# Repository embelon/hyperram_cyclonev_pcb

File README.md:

# Expansion PCB for Cyclone V SoC Development Kit

Using HSMC connector.

On board:
- 8MB HyperRAM memory: S27KL0641DABHI020
- 16MB HyperFlash : S26KL128SDABHI020
- 4MB QSPI FlashNOR: W25Q32JVSSIQ

I/O
- HDMI output
- 2 x PMOD (3V3): PMOD1 (J6), PMOD2 (7)
- 1 x PMOD (3V3 or 5V): PMOD3 (J5)
- 8bit LA header (shared signals with PMOD3/J5)
- 7 debug signals

### Images

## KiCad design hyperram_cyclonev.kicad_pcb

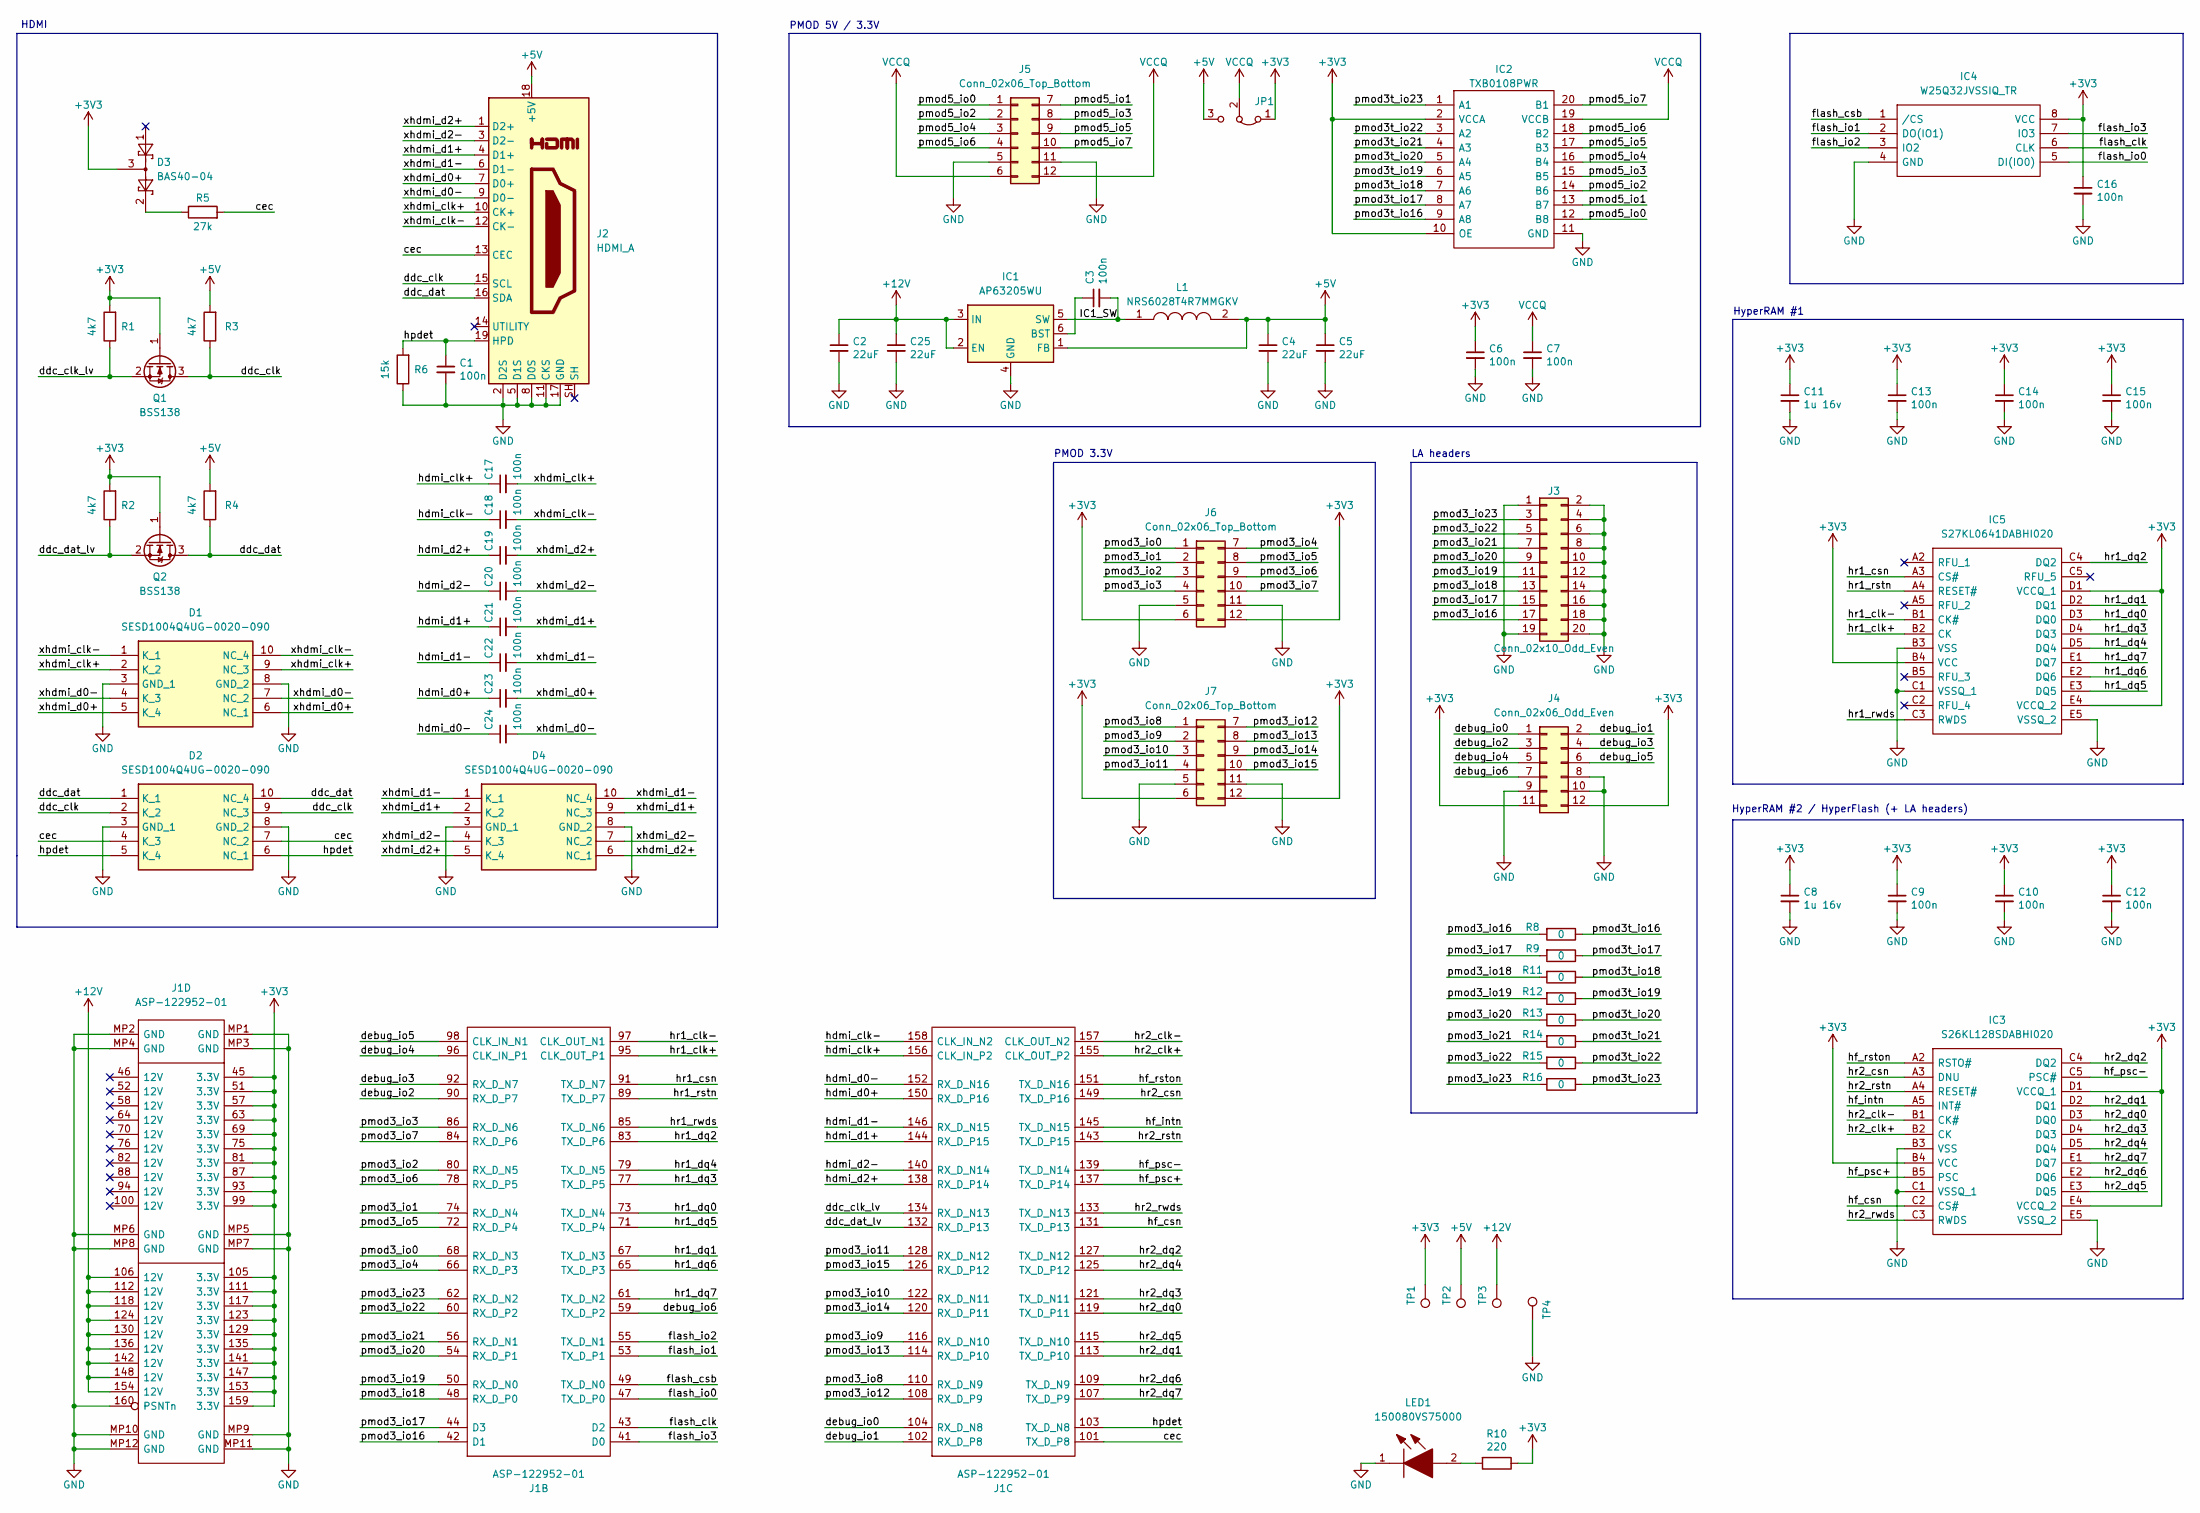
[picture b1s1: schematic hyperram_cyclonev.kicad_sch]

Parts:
C1, C9, C10, C12, C13, C14, C15, C16: 100n; C_0603_1608Metric_Pad1.08x0.95mm_HandSolder; Part CGA3E2X7R1H223K080AA
C2, C4, C5, C25: 22uF; C_0805_2012Metric_Pad1.18x1.45mm_HandSolder; Part CL21A226MAYNNNE
C3, C6, C7: 100n; C_0603_1608Metric_Pad1.08x0.95mm_HandSolder; Part 06033C104KAT2A
C8, C11: 1u 16v; C_0805_2012Metric_Pad1.18x1.45mm_HandSolder; Part CL10A105KO8NNNC
C17, C18, C19, C20, C21, C22, C23, C24: 100n; C_0402_1005Metric_Pad0.74x0.62mm_HandSolder; Part 06033C104KAT2A
D1, D2, D4: SESD1004Q4UG-0020-090; SESD1004Q4UG0020090; Mouser Part Number 650-SESD1004Q4UG0020
D3: BAS40-04; SOT-23
IC1: AP63205WU; TSOT-23-6
IC2: TXB0108PWR; SOP65P640X120-20N; Mouser Part Number 595-TXB0108PWR
IC3: S26KL128SDABHI020; BGA24C100P5X5_600X800X100; Mouser Part Number 727-S26KL128SDABHI02
IC4: W25Q32JVSSIQ_TR; SOIC127P790X216-8N; Mouser Part Number 454-W25Q32JVSSIQTR
IC5: S27KL0641DABHI020; BGA24C100P5X5_600X800X100; Manufacturer_Part_Number S27KL0641DABHI020; Mouser Part Number 727-S27KL0641DABHI02
J1: ASP-122952-01; ASP12295201; Manufacturer_Part_Number ASP-122952-01; Mouser Part Number 200-ASP-122952-01
J2: HDMI_A; 685119134923
J3: Conn_02x10_Odd_Even; PinHeader_2x10_P2.54mm_Vertical
J4: Conn_02x06_Odd_Even; PinHeader_2x06_P2.54mm_Vertical
J5, J6, J7: Conn_02x06_Top_Bottom; 610112249221_PMOD_Bottom
JP1: Jumper_3_Bridged12; PinHeader_1x03_P2.54mm_Vertical
L1: NRS6028T4R7MMGKV; NRS6028T4R7MMGK; Mouser Part Number 963-NRS6028T4R7MMGKV
LED1: 150080VS75000; LEDC2012X80N; Mouser Part Number 710-150080VS75000
Q1, Q2: BSS138; SOT-23
R1, R2, R3, R4: 4k7; R_0603_1608Metric_Pad0.98x0.95mm_HandSolder
R5: 27k; R_0603_1608Metric_Pad0.98x0.95mm_HandSolder
R6: 15k; R_0603_1608Metric_Pad0.98x0.95mm_HandSolder
R8, R9, R11, R12, R13, R14, R15, R16: 0; R_0402_1005Metric_Pad0.72x0.64mm_HandSolder
R10: 220; R_0603_1608Metric_Pad0.98x0.95mm_HandSolder; Part ‎RC0603JR-07100RL‎
TP1: 3V3; TestPoint_Pad_D1.0mm
TP2: 5V; TestPoint_Pad_D1.0mm
TP3: 12V; TestPoint_Pad_D1.0mm
TP4: GND; TestPoint_Pad_D1.0mm

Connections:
+3V3: C6.1, C8.1, C9.1, C10.1, C11.1, C12.1, C13.1, C14.1, C15.1, C16.1, D3.3, IC2.2 (VCCA), IC2.10 (OE), IC3.B4 (VCC), IC3.D1 (VCCQ_1), IC3.E4 (VCCQ_2), IC4.8 (VCC), IC5.B4 (VCC), IC5.D1 (VCCQ_1), IC5.E4 (VCCQ_2), J1.45 (3.3V), J1.51 (3.3V), J1.57 (3.3V), J1.63 (3.3V), J1.69 (3.3V), J1.75 (3.3V), J1.81 (3.3V), J1.87 (3.3V), J1.93 (3.3V), J1.99 (3.3V), J1.105 (3.3V), J1.111 (3.3V), J1.117 (3.3V), J1.123 (3.3V), J1.129 (3.3V), J1.135 (3.3V), J1.141 (3.3V), J1.147 (3.3V), J1.153 (3.3V), J1.159 (3.3V), J4.11, J4.12, J6.6, J6.12, J7.6, J7.12, JP1.1 (A), Q1.1 (G), Q2.1 (G), R1.2, R2.2, R10.1, TP1.1
+5V: C4.1, C5.1, IC1.1 (FB), J2.18 (+5V), JP1.3 (B), L1.2, R3.2, R4.2, TP2.1
+12V: C2.1, C25.1, IC1.2 (EN), IC1.3 (IN), J1.106 (12V), J1.112 (12V), J1.118 (12V), J1.124 (12V), J1.130 (12V), J1.136 (12V), J1.142 (12V), J1.148 (12V), J1.154 (12V), TP3.1
/IC1_SW: C3.2, IC1.5 (SW), L1.1
/cec: D2.4 (K_3), D2.7 (NC_2), J1.101 (TX_D_P8), J2.13 (CEC), R5.2
/ddc_clk: D2.2 (K_2), D2.9 (NC_3), J2.15 (SCL), Q1.3 (D), R3.1
/ddc_clk_lv: J1.134 (RX_D_N13), Q1.2 (S), R1.1
/ddc_dat: D2.1 (K_1), D2.10 (NC_4), J2.16 (SDA), Q2.3 (D), R4.1
/ddc_dat_lv: J1.132 (RX_D_P13), Q2.2 (S), R2.1
/debug_io0: J1.104 (RX_D_N8), J4.1
/debug_io1: J1.102 (RX_D_P8), J4.2
/debug_io2: J1.90 (RX_D_P7), J4.3
/debug_io3: J1.92 (RX_D_N7), J4.4
/debug_io4: J1.96 (CLK_IN_P1), J4.5
/debug_io5: J1.98 (CLK_IN_N1), J4.6
/debug_io6: J1.59 (TX_D_P2), J4.7
/flash_clk: IC4.6 (CLK), J1.43 (D2)
/flash_csb: IC4.1 (/CS), J1.49 (TX_D_N0)
/flash_io0: IC4.5 (DI(IO0)), J1.47 (TX_D_P0)
/flash_io1: IC4.2 (DO(IO1)), J1.53 (TX_D_P1)
/flash_io2: IC4.3 (IO2), J1.55 (TX_D_N1)
/flash_io3: IC4.7 (IO3), J1.41 (D0)
/hdmi_clk+: C17.1, J1.156 (CLK_IN_P2)
/hdmi_clk-: C18.1, J1.158 (CLK_IN_N2)
/hdmi_d0+: C23.1, J1.150 (RX_D_P16)
/hdmi_d0-: C24.1, J1.152 (RX_D_N16)
/hdmi_d1+: C21.1, J1.144 (RX_D_P15)
/hdmi_d1-: C22.1, J1.146 (RX_D_N15)
/hdmi_d2+: C19.1, J1.138 (RX_D_P14)
/hdmi_d2-: C20.1, J1.140 (RX_D_N14)
/hf_csn: IC3.C2 (CS#), J1.131 (TX_D_P13)
/hf_intn: IC3.A5 (INT#), J1.145 (TX_D_N15)
/hf_psc+: IC3.B5 (PSC), J1.137 (TX_D_P14)
/hf_psc-: IC3.C5 (PSC#), J1.139 (TX_D_N14)
/hf_rston: IC3.A2 (RSTO#), J1.151 (TX_D_N16)
/hpdet: C1.1, D2.5 (K_4), D2.6 (NC_1), J1.103 (TX_D_N8), J2.19 (HPD), R6.2
/hr1_clk+: IC5.B2 (CK), J1.95 (CLK_OUT_P1)
/hr1_clk-: IC5.B1 (CK#), J1.97 (CLK_OUT_N1)
/hr1_csn: IC5.A3 (CS#), J1.91 (TX_D_N7)
/hr1_dq0: IC5.D3 (DQ0), J1.73 (TX_D_N4)
/hr1_dq1: IC5.D2 (DQ1), J1.67 (TX_D_N3)
/hr1_dq2: IC5.C4 (DQ2), J1.83 (TX_D_P6)
/hr1_dq3: IC5.D4 (DQ3), J1.77 (TX_D_P5)
/hr1_dq4: IC5.D5 (DQ4), J1.79 (TX_D_N5)
/hr1_dq5: IC5.E3 (DQ5), J1.71 (TX_D_P4)
/hr1_dq6: IC5.E2 (DQ6), J1.65 (TX_D_P3)
/hr1_dq7: IC5.E1 (DQ7), J1.61 (TX_D_N2)
/hr1_rstn: IC5.A4 (RESET#), J1.89 (TX_D_P7)
/hr1_rwds: IC5.C3 (RWDS), J1.85 (TX_D_N6)
/hr2_clk+: IC3.B2 (CK), J1.155 (CLK_OUT_P2)
/hr2_clk-: IC3.B1 (CK#), J1.157 (CLK_OUT_N2)
/hr2_csn: IC3.A3 (DNU), J1.149 (TX_D_P16)
/hr2_dq0: IC3.D3 (DQ0), J1.119 (TX_D_P11)
/hr2_dq1: IC3.D2 (DQ1), J1.113 (TX_D_P10)
/hr2_dq2: IC3.C4 (DQ2), J1.127 (TX_D_N12)
/hr2_dq3: IC3.D4 (DQ3), J1.121 (TX_D_N11)
/hr2_dq4: IC3.D5 (DQ4), J1.125 (TX_D_P12)
/hr2_dq5: IC3.E3 (DQ5), J1.115 (TX_D_N10)
/hr2_dq6: IC3.E2 (DQ6), J1.109 (TX_D_N9)
/hr2_dq7: IC3.E1 (DQ7), J1.107 (TX_D_P9)
/hr2_rstn: IC3.A4 (RESET#), J1.143 (TX_D_P15)
/hr2_rwds: IC3.C3 (RWDS), J1.133 (TX_D_N13)
/pmod3_io0: J1.68 (RX_D_N3), J6.1
/pmod3_io1: J1.74 (RX_D_N4), J6.2
/pmod3_io2: J1.80 (RX_D_N5), J6.3
/pmod3_io3: J1.86 (RX_D_N6), J6.4
/pmod3_io4: J1.66 (RX_D_P3), J6.7
/pmod3_io5: J1.72 (RX_D_P4), J6.8
/pmod3_io6: J1.78 (RX_D_P5), J6.9
/pmod3_io7: J1.84 (RX_D_P6), J6.10
/pmod3_io8: J1.110 (RX_D_N9), J7.1
/pmod3_io9: J1.116 (RX_D_N10), J7.2
/pmod3_io10: J1.122 (RX_D_N11), J7.3
/pmod3_io11: J1.128 (RX_D_N12), J7.4
/pmod3_io12: J1.108 (RX_D_P9), J7.7
/pmod3_io13: J1.114 (RX_D_P10), J7.8
/pmod3_io14: J1.120 (RX_D_P11), J7.9
/pmod3_io15: J1.126 (RX_D_P12), J7.10
/pmod3_io16: J1.42 (D1), J3.17, R8.2
/pmod3_io17: J1.44 (D3), J3.15, R9.2
/pmod3_io18: J1.48 (RX_D_P0), J3.13, R11.2
/pmod3_io19: J1.50 (RX_D_N0), J3.11, R12.2
/pmod3_io20: J1.54 (RX_D_P1), J3.9, R13.2
/pmod3_io21: J1.56 (RX_D_N1), J3.7, R14.2
/pmod3_io22: J1.60 (RX_D_P2), J3.5, R15.2
/pmod3_io23: J1.62 (RX_D_N2), J3.3, R16.2
/pmod3t_io16: IC2.9 (A8), R8.1
/pmod3t_io17: IC2.8 (A7), R9.1
/pmod3t_io18: IC2.7 (A6), R11.1
/pmod3t_io19: IC2.6 (A5), R12.1
/pmod3t_io20: IC2.5 (A4), R13.1
/pmod3t_io21: IC2.4 (A3), R14.1
/pmod3t_io22: IC2.3 (A2), R15.1
/pmod3t_io23: IC2.1 (A1), R16.1
/pmod5_io0: IC2.12 (B8), J5.1
/pmod5_io1: IC2.13 (B7), J5.7
/pmod5_io2: IC2.14 (B6), J5.2
/pmod5_io3: IC2.15 (B5), J5.8
/pmod5_io4: IC2.16 (B4), J5.3
/pmod5_io5: IC2.17 (B3), J5.9
/pmod5_io6: IC2.18 (B2), J5.4
/pmod5_io7: IC2.20 (B1), J5.10
/xhdmi_clk+: C17.2, D1.2 (K_2), D1.9 (NC_3), J2.10 (CK+)
/xhdmi_clk-: C18.2, D1.1 (K_1), D1.10 (NC_4), J2.12 (CK-)
/xhdmi_d0+: C23.2, D1.5 (K_4), D1.6 (NC_1), J2.7 (D0+)
/xhdmi_d0-: C24.2, D1.4 (K_3), D1.7 (NC_2), J2.9 (D0-)
/xhdmi_d1+: C21.2, D4.2 (K_2), D4.9 (NC_3), J2.4 (D1+)
/xhdmi_d1-: C22.2, D4.1 (K_1), D4.10 (NC_4), J2.6 (D1-)
/xhdmi_d2+: C19.2, D4.5 (K_4), D4.6 (NC_1), J2.1 (D2+)
/xhdmi_d2-: C20.2, D4.4 (K_3), D4.7 (NC_2), J2.3 (D2-)
GND: C1.2, C2.2, C4.2, C5.2, C6.2, C7.2, C8.2, C9.2, C10.2, C11.2, C12.2, C13.2, C14.2, C15.2, C16.2, C25.2, D1.3 (GND_1), D1.8 (GND_2), D2.3 (GND_1), D2.8 (GND_2), D4.3 (GND_1), D4.8 (GND_2), IC1.4 (GND), IC2.11 (GND), IC3.B3 (VSS), IC3.C1 (VSSQ_1), IC3.E5 (VSSQ_2), IC4.4 (GND), IC5.B3 (VSS), IC5.C1 (VSSQ_1), IC5.E5 (VSSQ_2), J1.160 (PSNTn), J1.MP1 (GND), J1.MP2 (GND), J1.MP3 (GND), J1.MP4 (GND), J1.MP5 (GND), J1.MP6 (GND), J1.MP7 (GND), J1.MP8 (GND), J1.MP9 (GND), J1.MP10 (GND), J1.MP11 (GND), J1.MP12 (GND), J2.2 (D2S), J2.5 (D1S), J2.8 (D0S), J2.11 (CKS), J2.17 (GND), J3.1, J3.2, J3.4, J3.6, J3.8, J3.10, J3.12, J3.14, J3.16, J3.18, J3.19, J3.20, J4.8, J4.9, J4.10, J5.5, J5.11, J6.5, J6.11, J7.5, J7.11, LED1.1, R6.1, TP4.1
unnamed: D3.2, R5.1
unnamed: C3.1, IC1.6 (BST)
unnamed: LED1.2, R10.2
VCCQ: C7.1, IC2.19 (VCCB), J5.6, J5.12, JP1.2 (C)

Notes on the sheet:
PMOD 3.3V
LA headers
HDMI
HyperRAM #2 / HyperFlash (+ LA headers)
HyperRAM #1
PMOD 5V / 3.3V

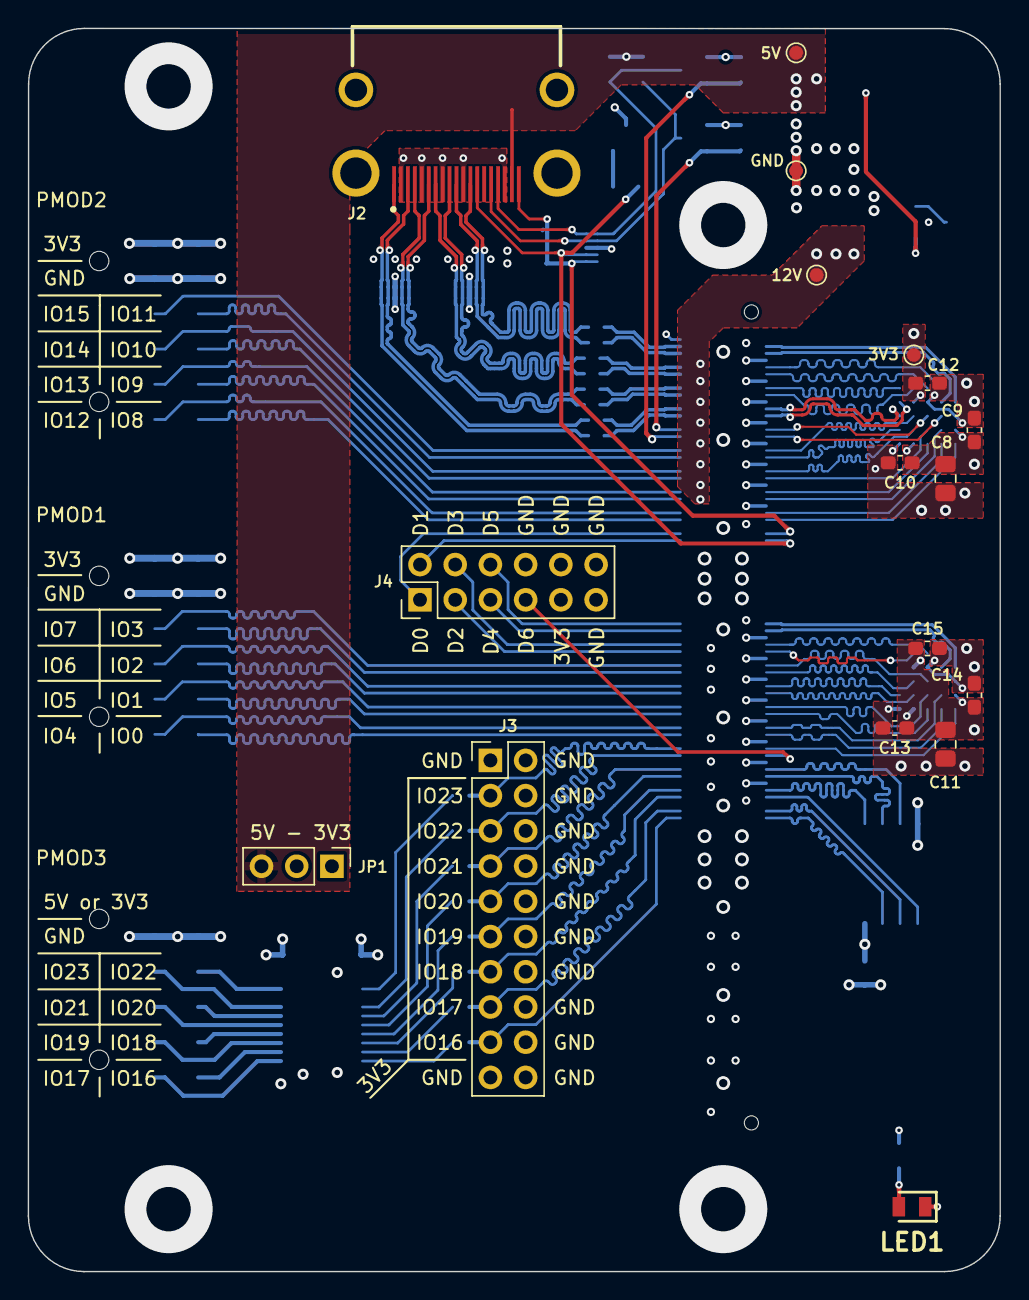
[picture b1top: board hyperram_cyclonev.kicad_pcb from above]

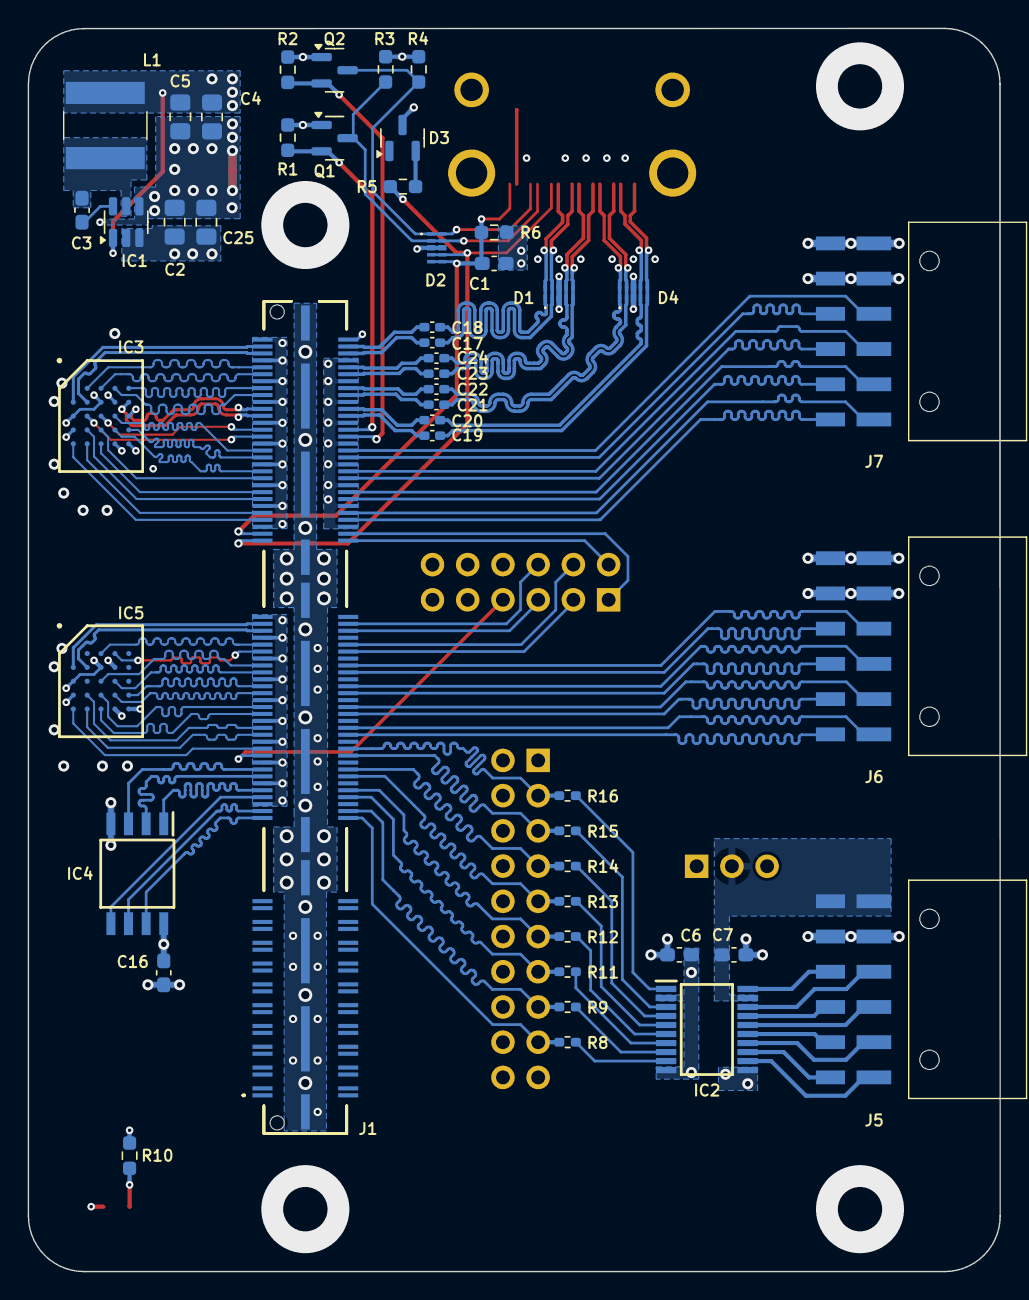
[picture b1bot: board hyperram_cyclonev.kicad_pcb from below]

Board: 4 copper layers, 70.1 x 89.6 mm, 65 parts (48 on the bottom side), 115 nets.

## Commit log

2022-09-15 Added PCB library
2022-10-16 Added DC/DC converter to get 5V for PMOD and HDMI from 12V. Changed two TXB0104 to one TXB0108 for PMOD 5V.
2022-10-24 Updated schematics, made connections between PMODs, HyperBUS devices, Debug Header, QSPI NOR Flash, HDMI and HSMC.
2023-08-11 Migrated to KiCad 7.
2023-08-11 Added 100nF capacitors in series for HDMI signals to get TMDS working with LVDS3 outputs on FPGA.
2023-08-15 Fixed 2 issues with unconnected signals.
2023-08-15 Updated symbols and footprints libraries.
2024-05-12 Fixed Schematics DRC warnings
2024-05-13 Decreased number of ERC complaints. Assigned missing packages.
2024-05-13 Loaded components into PCB.
2024-05-14 Fixed PCB footprint for PMOD
2024-05-14 Updated PCB footprint for HSMC
2024-05-14 Simplified schematic, removing unnecessary elements
2024-05-14 Created edge.cuts. Updated PCB from schematic.
2024-05-15 Fixed issue with PMOD pins assignment
2024-05-16 Adjusted PCB dimensions. Moved components to the back side
2024-05-17 Changed two connectors from SMD to THT
2024-05-17 Rearrange signals assignments to simplify routing.
2024-05-17 Changed footprint in library from SMD to THT
2024-05-17 Added modified pinouts for PMOD, top and bottom version
2024-05-17 Reaarranged signals assignments to simplify routing
2024-05-22 Set constraints for PCBWay: 6/6mil, hole 0.25mm. First try for routing HyperRAM with trace length matching.
2024-05-23 Optimizing signal assigments and component placement to simplify routing.
2024-05-27 Fixed differential pairs designators for HyperRAM clk and psc and HDMI clk and data.
2024-06-11 Changed order of HDMI data signals to avoid crossing
2024-06-11 Decreased board area. Fixed HyperRAM clk diff pair routing. First try for HDMI diff pair routing.
2024-06-12 Added additional resistors on LA / PMOD path
2024-06-12 Routed almost all single ended signals, except HDMI and power
2024-06-13 Added net class for HDMI differential signals
2024-06-13 Routed HDMI differential signals for a first time, still with unmatched lenghts between pairs
2024-06-14 Added width/space definition for differential traces
2024-06-14 Fixed pin numbering for SESD Series TVS Diode Array
2024-06-14 Fixed signals connection to SESD Series TVS Diode Array
2024-06-14 Decreased courtyyard/keepout area for SESD Series TVS Diode Array in DFN 0802 package
2024-06-14 Fixed path to package definition library from absolute to relative
2024-06-14 Updated PCB with latest fixes in schematic related to SESD Series TVS Diode Array
2024-06-18 Added symbol for new component SESD1004, TVS Diode Array, to the library
2024-06-18 Added footprint for new component SESD1004, TVS Diode Array, to the library
2024-06-18 Changed min clearance to 5mils, 0.127mm. Added new track 0,254mm.
2024-06-18 Changed SESD Series TVS Diode Array to different model. Rearranged schematic.
2024-06-18 Updated footprints for changed SESD Series TVS Diode Arrays
2024-06-18 Decreased courtyyard/keepout area for SESD Series TVS Diode Array in DFN 1004 package
2024-06-18 Updated SESD Series TVS Diode Arrays on PCB
2024-06-19 Fixed net class patterns for HDMI differential pairs
2024-06-19 Routed HDMI differential pairs with intra-pair lenght matching
2024-06-19 Equalized lenghts of HDMI differential pairs.
2024-06-19 Connected directly +5P with +5V power
2024-06-19 Changed clearance back to 0,1524mm / 6mils to route all except HDMI diff pairs
2024-06-19 Routed remaining HDMI signals. Routed DC/DC SWPS for +12V to +5V conversion
2024-06-21 Added filled areas for GND and 3V3 supplying HyperRAM memory
2024-06-21 Placed all local filled areas for 3V3, 5V, GND
2024-06-21 Added second filtering input capacitor for DC/DC converter
2024-06-21 Added GND and 3V3 fill areas
2024-06-21 Marked unused 12V pins as NC
2024-06-21 Fixed meaningful ERC errors in schematic
2024-06-21 Modified HDMI footprint to match schematic symbol (shielding connections)
2024-06-21 Fixed DRC errors
2024-06-21 Decreased number of shielding, return path Vias for GND around HDMI diff pairs
2024-06-21 Fixed DRC warnings related to f.silkscreen
2024-06-21 Fixed DRC warnings related to b.silkscreen
2024-06-21 Added signal names on f.silkscreen
2024-06-21 Updated project description
2024-06-21 Added render action for PCB
2024-06-22 Added teardrops to all tracks connected to vias. Refilled all areas again.
